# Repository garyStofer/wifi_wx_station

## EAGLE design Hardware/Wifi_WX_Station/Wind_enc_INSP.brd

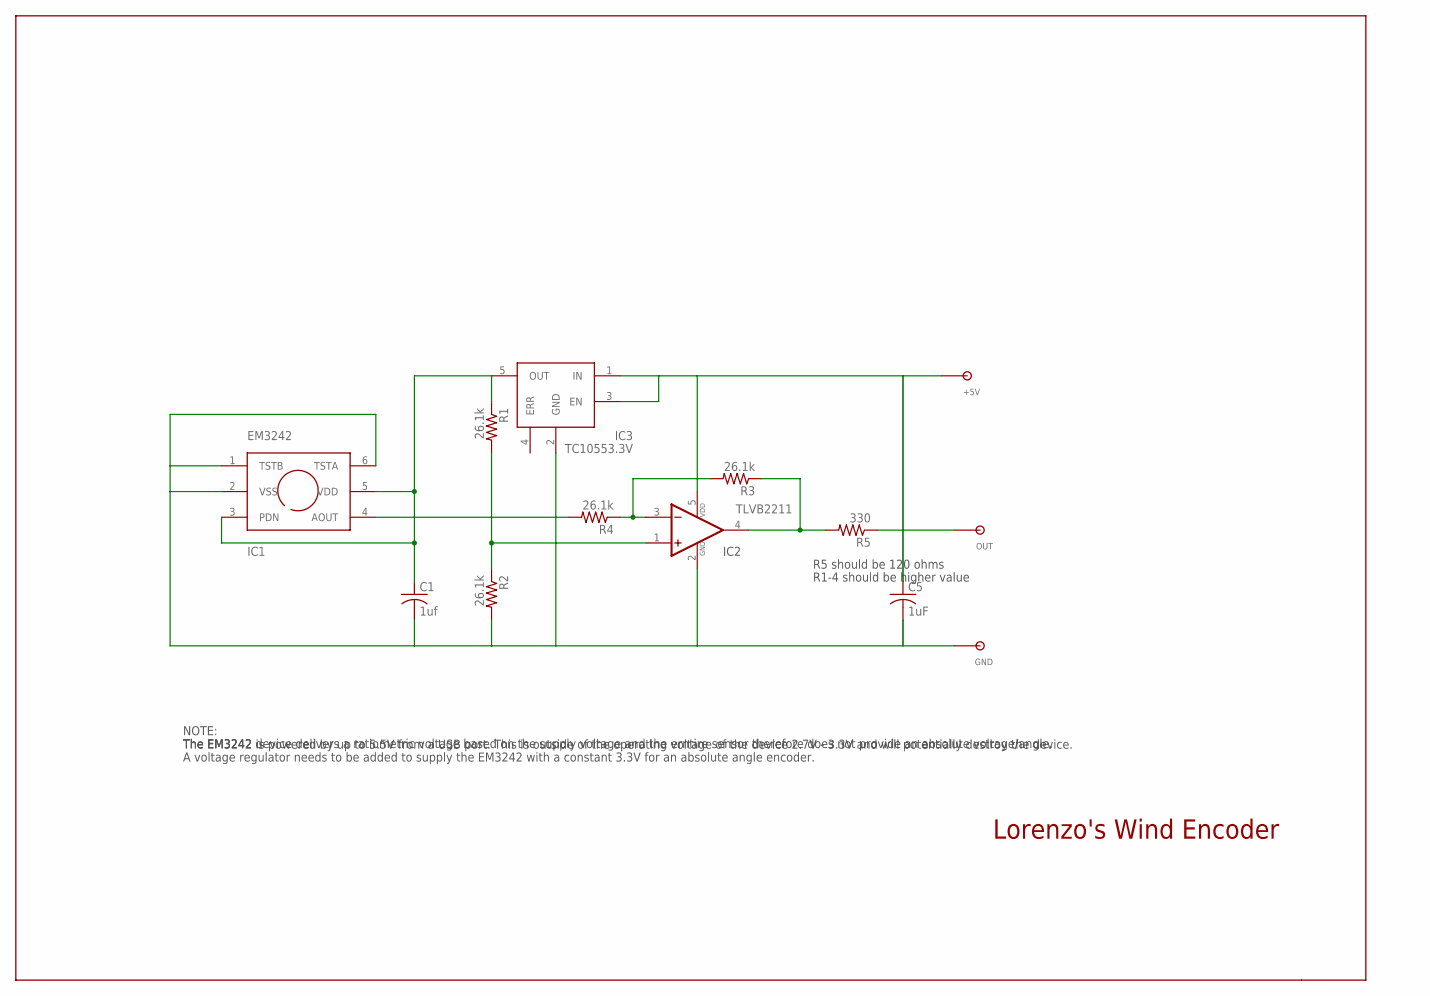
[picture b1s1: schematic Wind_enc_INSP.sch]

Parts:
+5V: TPSOL; TP_SOL
C1: 1uf; C0805K
C5: 1uF; C0805K
GND: TPSOL; TP_SOL
IC1: EM3242; EM3242_SPECIAL
IC2: TLVB2211; SOT23-5
IC3: TC10553.3V; SOT23-5
OUT: TPSOL; TP_SOL
R1, R2, R3, R4: 26.1k; R0603
R5: 330; R0603

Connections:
unnamed: +5V.P$1, C5.1, IC2.5 (VDD), IC3.1 (IN), IC3.3 (EN)
unnamed: C1.2, C5.2, GND.P$1, IC1.1 (TSTB), IC1.2 (VSS), IC1.6 (TSTA), IC2.2 (VDD_GND), IC3.2 (GND), R2.2
unnamed: OUT.P$1, R5.1
unnamed: IC1.4 (AOUT), R4.2
unnamed: C1.1, IC1.3 (PDN), IC1.5 (VDD), IC3.5 (OUT), R1.1
unnamed: IC2.3 (-IN), R3.2, R4.1
unnamed: IC2.4 (OUT), R3.1, R5.2
unnamed: IC2.1 (+IN), R1.2, R2.1

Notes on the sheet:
Lorenzo's Wind Encoder
NOTE: The EM3242 is powered by up to 5.5V from a USB port. This is outside of the operating voltage of the device 2.7V - 3.3V and will potentially destroy the device.
The EM3242 device delivers a ratiometric voltage based on the supply voltage and the erntire sensor therefore does not provide an absolute voltage/angle. A voltage regulator needs to be added to supply the EM3242 with a constant 3.3V for an absolute angle encoder.
R5 should be 120 ohms
R1-4 should be higher value
IC2

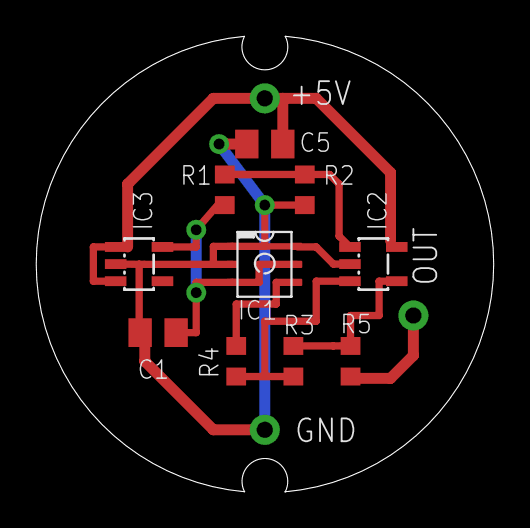
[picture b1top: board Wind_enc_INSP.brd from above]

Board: 2 copper layers, 25.4 x 25.3 mm, 13 parts (0 on the bottom side), 8 nets.

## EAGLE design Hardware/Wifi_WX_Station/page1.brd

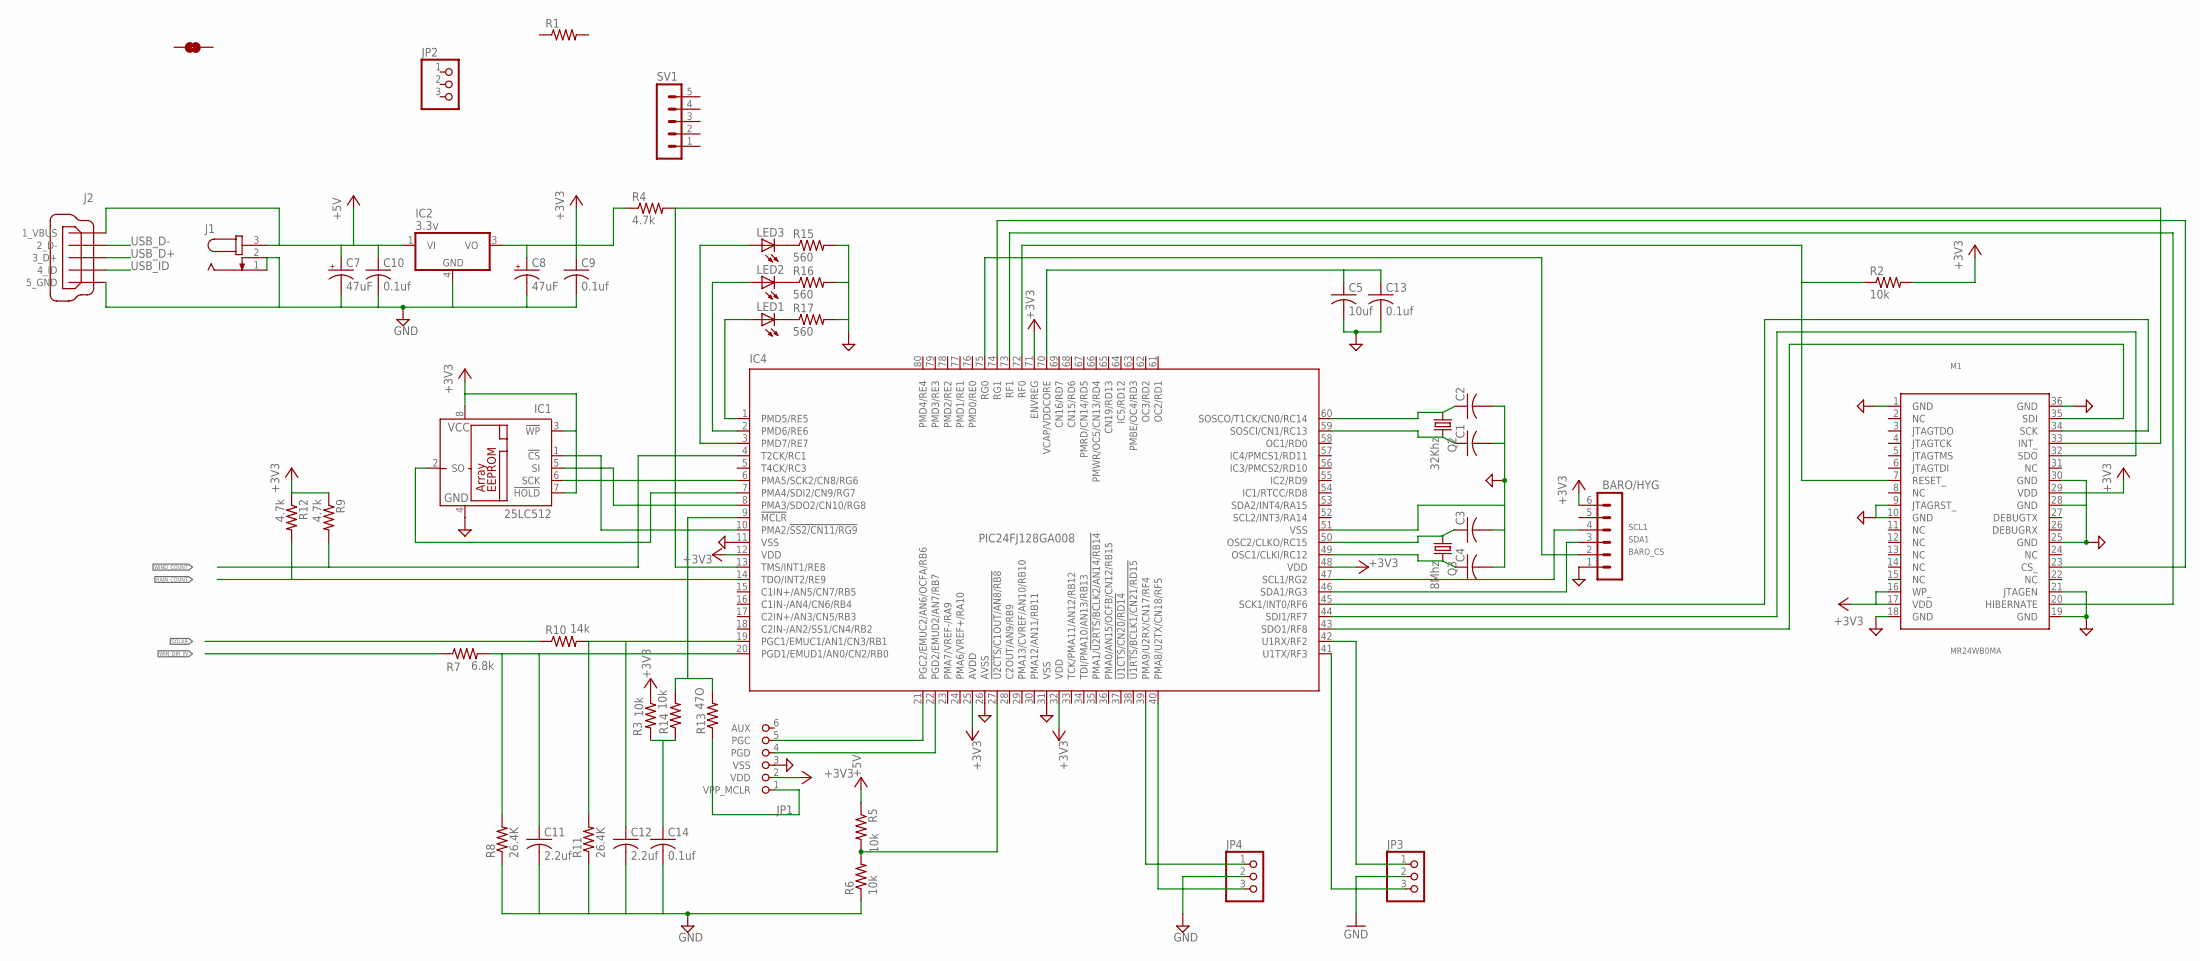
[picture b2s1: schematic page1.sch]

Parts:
BARO/HYG: MA06-1
C1, C2, C3, C4: C-USC0603; C0603
C5: 10uf; C0805
C7, C8: 47uF; 140CLH-0810
C9, C10, C13, C14: 0.1uf; C0805
C11, C12: 2.2uf; C1206
IC1: 25LC512; SO-08
IC2: 3.3v; DPACK
IC4: PIC24FJ128GA008; TQFP80-12X12
J1: JACK-PLUG0; SPC4077
J2: MINI-USB-32005-201; 32005-201
JP1: PIKIT2_PRG; 1X06
JP2, JP3, JP4: PINHD-1X3; 1X03
LED1, LED2, LED3: LEDCHIP-LED0603; CHIP-LED0603
M1: MR24WB0MA; MRF24W
Q2: 32Khz; TC26H
Q3: 8Mhz; HC49/S
R1: R-US_R0603; R0603
R2, R3, R5, R6, R14: 10k; R0603
R4, R9, R12: 4.7k; R0603
R7: 6.8k; R0603
R8, R11: 26.4K; R0603
R10: 14k; R0603
R13: 47O; R0603
R15, R16, R17: 560; R0603
SV1: MA05-1
U$2: SOLDERBRIDGE; SOLDER_BRIDGE

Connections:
+3V3: BARO/HYG.6, C8.+, C9.1, IC1.3 (!WP), IC1.7 (!HOLD), IC1.8 (VCC), IC2.3 (VO), IC4.12 (VDD), IC4.25 (AVDD), IC4.32 (VDD), IC4.48 (VDD), IC4.71 (ENVREG), JP1.2 (VDD), M1.16 (WP_), M1.17 (VDD), M1.29 (VDD), R2.2, R3.1, R4.1, R9.1, R12.1
+5V: C7.+, C10.1, IC2.1 (VI), J1.3, J2.1_VBUS, R5.1
BARO_CS: BARO/HYG.2, IC4.75 (RG0)
GND: BARO/HYG.1, C1.2, C2.2, C3.2, C4.2, C5.2, C7.-, C8.-, C9.2, C10.2, C11.2, C12.2, C13.2, C14.2, IC1.4 (GND), IC2.4 (GND), IC4.11 (VSS), IC4.26 (AVSS), IC4.31 (VSS), IC4.51 (VSS), J1.1, J1.2, J2.5_USB_GND (5_GND), JP1.3 (VSS), JP3.2, JP4.2, M1.1 (GND), M1.9 (JTAGRST_), M1.10 (GND), M1.18 (GND), M1.19 (GND), M1.21 (JTAGEN), M1.25 (GND), M1.28 (GND), M1.30 (GND), M1.36 (GND), R6.1, R8.1, R11.1, R15.2, R16.2, R17.2
unnamed: C2.1, IC4.60 (SOSCO/T1CK/CN0/RC14), Q2.1
unnamed: C1.1, IC4.59 (SOSCI/CN1/RC13), Q2.2
unnamed: IC4.42 (U1RX/RF2), JP3.1
unnamed: C3.1, IC4.50 (OSC2/CLKO/RC15), Q3.1
unnamed: C4.1, IC4.49 (OSC1/CLKI/RC12), Q3.2
unnamed: IC4.41 (U1TX/RF3), JP3.3
unnamed: IC4.40 (PMA8/U2TX/CN18/RF5), JP4.3
unnamed: IC4.39 (PMA9/U2RX/CN17/RF4), JP4.1
unnamed: IC4.73 (RF1), M1.20 (HIBERNATE)
unnamed: IC4.72 (RF0), M1.7 (RESET_), R2.1
unnamed: IC4.45 (SCK1/INT0/RF6), M1.34 (SCK)
unnamed: IC4.44 (SDI1/RF7), M1.32 (SDO)
unnamed: IC4.43 (SDO1/RF8), M1.35 (SDI)
unnamed: IC4.27 (!U2CTS/C1OUT/AN8/RB8), R5.2, R6.2
unnamed: IC4.74 (RG1), M1.23 (CS_)
unnamed: IC4.21 (PGC2/EMUC2/AN6/OCFA/RB6), JP1.5 (PGC)
unnamed: IC4.22 (PGD2/EMUD2/AN7/RB7), JP1.4 (PGD)
unnamed: C12.1, IC4.19 (PGC1/EMUC1/AN1/CN3/RB1), R10.2, R11.2
unnamed: C5.1, C13.1, IC4.70 (VCAP/VDDCORE)
unnamed: IC4.9 (!MCLR), R13.2, R14.2
unnamed: C11.1, IC4.20 (PGD1/EMUD1/AN0/CN2/RB0), R7.2, R8.2
unnamed: C14.1, R3.2, R14.1
unnamed: LED1.C, R17.1
unnamed: JP1.1 (VPP_MCLR), R13.1
unnamed: IC1.2 (SO), IC4.7 (PMA4/SDI2/CN9/RG7)
unnamed: IC4.13 (TMS/INT1/RE8), M1.33 (INT_), R4.2
unnamed: IC1.1 (!CS), IC4.10 (PMA2/!SS2/CN11/RG9)
unnamed: LED2.C, R16.1
unnamed: IC1.6 (SCK), IC4.6 (PMA5/SCK2/CN8/RG6)
unnamed: LED3.C, R15.1
unnamed: IC4.1 (PMD5/RE5), LED1.A
unnamed: IC1.5 (SI), IC4.8 (PMA3/SDO2/CN10/RG8)
unnamed: IC4.2 (PMD6/RE6), LED2.A
unnamed: IC4.3 (PMD7/RE7), LED3.A
RAIN_COUNT: IC4.14 (TDO/INT2/RE9), R12.2
SCL1: BARO/HYG.4, IC4.47 (SCL1/RG2)
SDA1: BARO/HYG.3, IC4.46 (SDA1/RG3)
SOLAR: R10.1
USB_D+: J2.3_D+
USB_D-: J2.2_D-
USB_ID: J2.4_ID
WIND_COUNT: IC4.4 (T2CK/RC1), R9.2
WIN_DIR_IN: R7.1

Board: 2 copper layers, 48 parts (0 on the bottom side), 42 nets, no tracks yet.

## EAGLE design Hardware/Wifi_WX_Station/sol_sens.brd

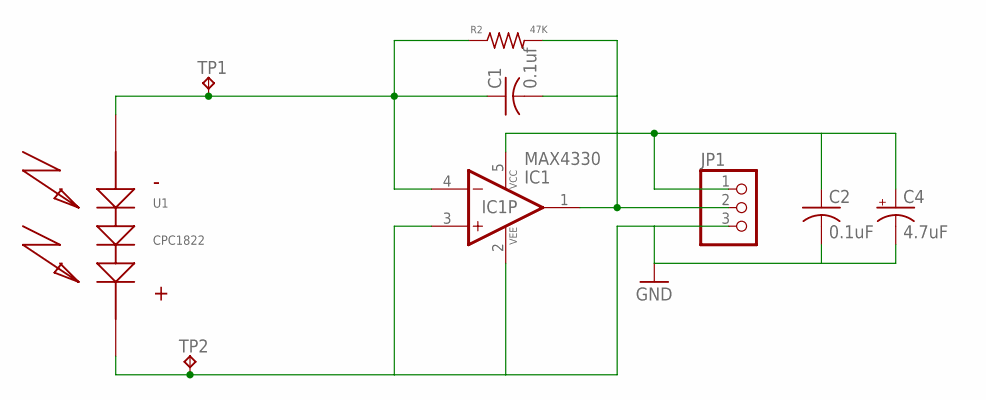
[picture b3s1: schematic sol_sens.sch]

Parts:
C1: 0.1uf; C0805
C2: 0.1uF; C0805
C4: 4.7uF; R/2012-12R
IC1: MAX4330; SOT23-5
JP1: PINHD-1X3; 1X03
R2: 47K; R0805
TP1, TP2: TPB1,27; B1,27
U1: CPC1822; SO08

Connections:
GND: C2.2, C4.-, IC1.2 (VEE), IC1.3 (+IN), JP1.3, TP2.PP, U1.8 (V+)
unnamed: C1.1, IC1.4 (-IN), R2.1, TP1.PP, U1.5 (V-)
unnamed: C1.2, IC1.1 (OUT), JP1.2, R2.2
unnamed: C2.1, C4.+, IC1.5 (VCC), JP1.1

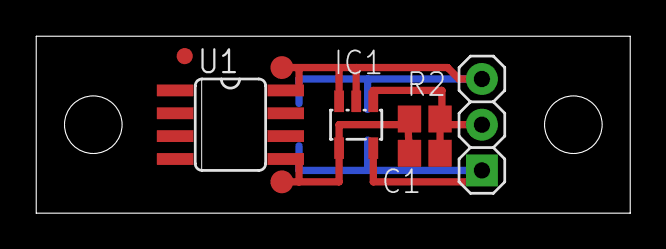
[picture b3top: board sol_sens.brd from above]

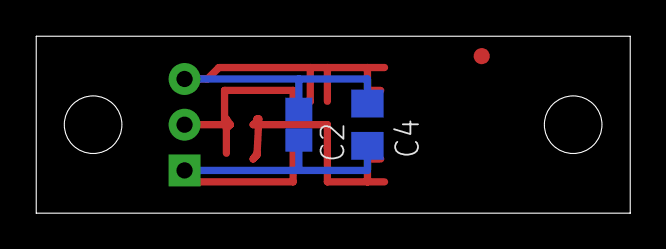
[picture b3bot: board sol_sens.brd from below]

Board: 2 copper layers, 33.0 x 9.8 mm, 9 parts (2 on the bottom side), 4 nets.
